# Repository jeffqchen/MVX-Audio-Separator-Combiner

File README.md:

# MVX-Audio-Separator-Combiner
An Audio Signal Separator & Combiner for the Extron MVX Switch

This is a dongle for separating and combining audio from/into VGA pin 12 and 15 and output from a 3.5mm jack, in order to interface with the Extron MVX VGA switch.

It's only necessary when you transmit audio through the VGA cable into/out of the Extron MVX switch.

-------

## Parts

Here are the necessary parts:

- PCB - 2 PCB per assembly - [Link](https://oshpark.com/shared_projects/WU69JtAB)

*If you wish to break out the audio from the VGA cable at any time, you can make just ONE of these PCB and use it.*

- VGA Port Slim Female - [Link](https://github.com/jeffqchen/JeffParts/blob/main/Connectors/HD15/Slim/Female%20PCB/info.md)

- VGA Port Male Slim - [Link](https://github.com/jeffqchen/JeffParts/blob/main/Connectors/HD15/Slim/Male%20PCB/info.md)

- Vertical 3.5mm Headphone Jack - [Link](https://github.com/jeffqchen/JeffParts/blob/main/Connectors/3.5mm%20Audio%20Jack/Vertical%205-Pin%20PCB/info.md)

- [2x] M3x20mm screw & nut - [Link](https://github.com/jeffqchen/JeffParts/blob/main/Parts/M2%20M3%20Hex%20Screw%20%26%20Nut/info.md)

- VGA Thumb Screw - [Link](https://github.com/jeffqchen/JeffParts/blob/main/Parts/VGA%20Thumb%20Screw/info.md)

- 3.5mm Audio Jumper Cable - [Link](https://github.com/jeffqchen/JeffParts/blob/main/Parts/3.5mm%20Audio%20Jumper%20Cable/info.md)

- 3D Printed Shells

-------

## Assembly

Solder the VGA ports according to the silk screen print. Make sure the ports sit tightly on top of the PCB. Solder two copies of the PCB assembly. Make sure to trim the extra length of the pins of the audio jack for the upper assembly, or it will interfere with the bottom assembly.

Insert two nuts into the slot inside the right shell

Insert the two PCB assembly into the right shell

Close the left shell onto the right. Then screw in the two M3x20 screws. Do not over tighten the screws, or the nuts would break free inside the slots.

Last, screw in the thumb screw.

-----

## Misc
Due to the space restriction behind the MVX switch, you will need a audio jumper cable with both ends in a right angle for clearance. Here is an example:
- https://www.aliexpress.com/item/4000465962340.html

-----
Shield: [![CC BY-SA 4.0][cc-by-sa-shield]][cc-by-sa]

This work is licensed under a
[Creative Commons Attribution-ShareAlike 4.0 International License][cc-by-sa].

[![CC BY-SA 4.0][cc-by-sa-image]][cc-by-sa]

[cc-by-sa]: http://creativecommons.org/licenses/by-sa/4.0/
[cc-by-sa-image]: https://licensebuttons.net/l/by-sa/4.0/88x31.png
[cc-by-sa-shield]: https://img.shields.io/badge/License-CC%20BY--SA%204.0-lightgrey.svg

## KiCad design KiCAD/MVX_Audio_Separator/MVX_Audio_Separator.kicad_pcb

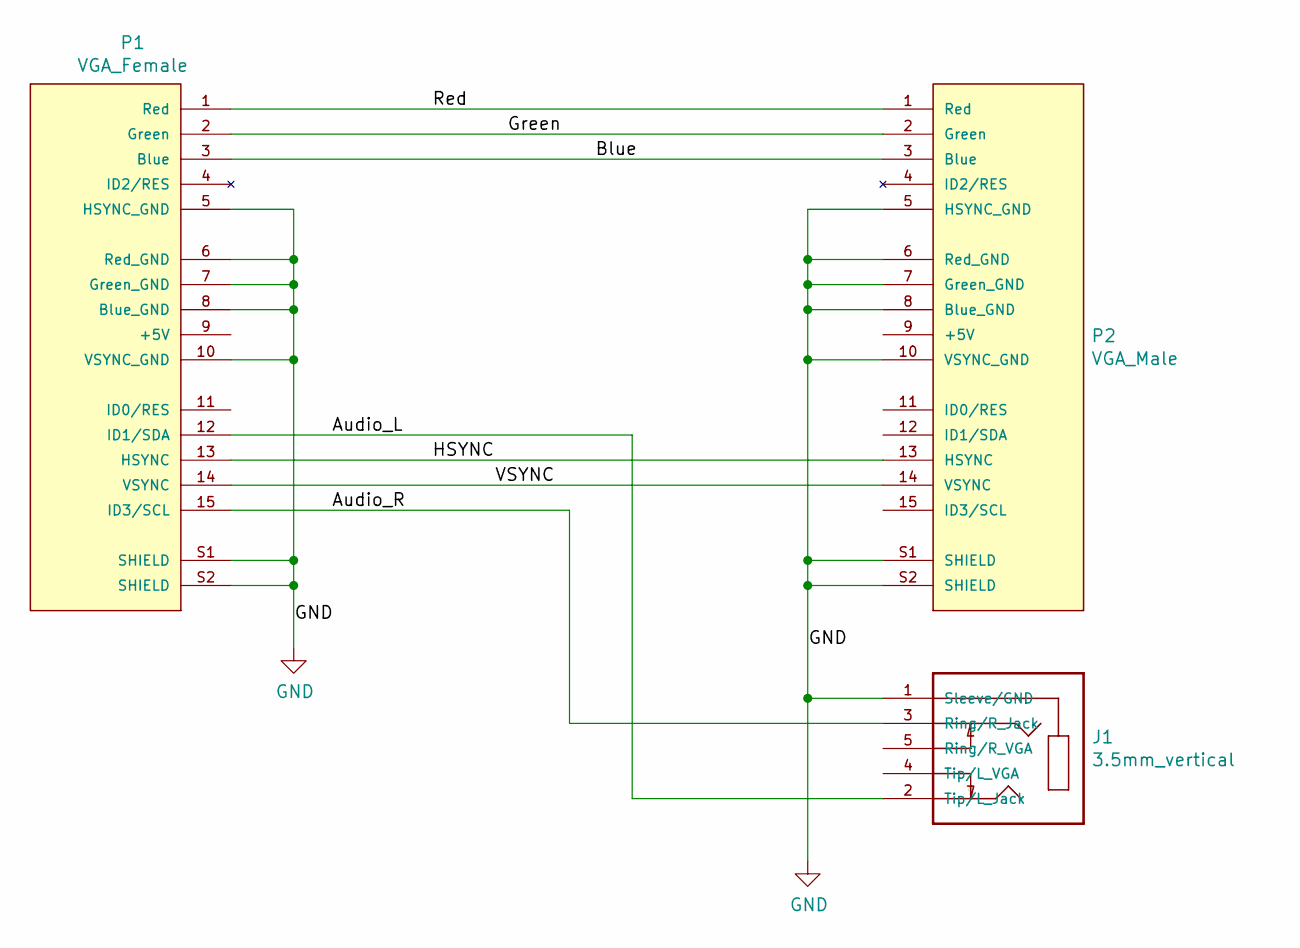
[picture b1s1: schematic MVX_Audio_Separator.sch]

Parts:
J1: 3.5mm_vertical; 3.5mm_Vertical; PARTREV 1.01
P1: VGA_Female; VGA_female_rightangle_slim; PARTREV N/A
P2: VGA_Male; VGA_male_rightangle_slim; PARTREV N/A

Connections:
/Audio_L: J1.2 (Tip/L_Jack), P1.12 (ID1/SDA)
/Audio_R: J1.3 (Ring/R_Jack), P1.15 (ID3/SCL)
/Blue: P1.3 (Blue), P2.3 (Blue)
/Green: P1.2 (Green), P2.2 (Green)
/HSYNC: P1.13 (HSYNC), P2.13 (HSYNC)
/Red: P1.1 (Red), P2.1 (Red)
/VSYNC: P1.14 (VSYNC), P2.14 (VSYNC)
GND: J1.1 (Sleeve/GND), P1.5 (HSYNC_GND), P1.6 (Red_GND), P1.7 (Green_GND), P1.8 (Blue_GND), P1.10 (VSYNC_GND), P1.S1 (SHIELD), P1.S2 (SHIELD), P2.5 (HSYNC_GND), P2.6 (Red_GND), P2.7 (Green_GND), P2.8 (Blue_GND), P2.10 (VSYNC_GND), P2.S1 (SHIELD), P2.S2 (SHIELD)

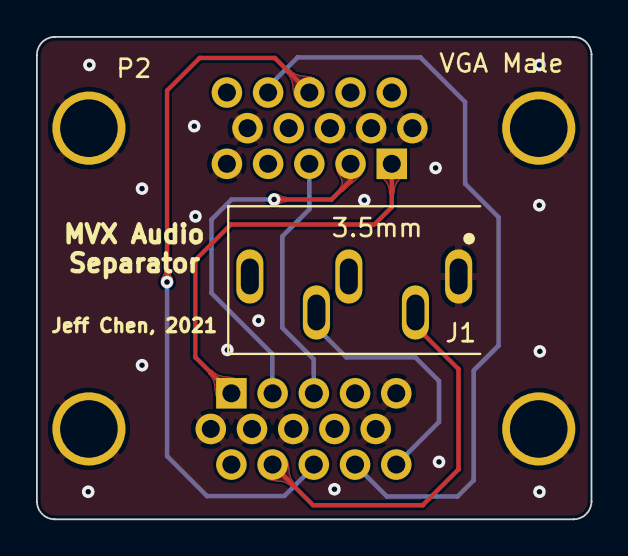
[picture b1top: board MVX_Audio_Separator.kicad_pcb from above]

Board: 2 copper layers, 30.8 x 26.8 mm, 3 parts (1 on the bottom side), 8 nets.

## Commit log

2021-10-04 Initial upload
2021-10-24 Update PCB
2021-11-30 Update 3D printed shell
2022-08-09 Change license type
